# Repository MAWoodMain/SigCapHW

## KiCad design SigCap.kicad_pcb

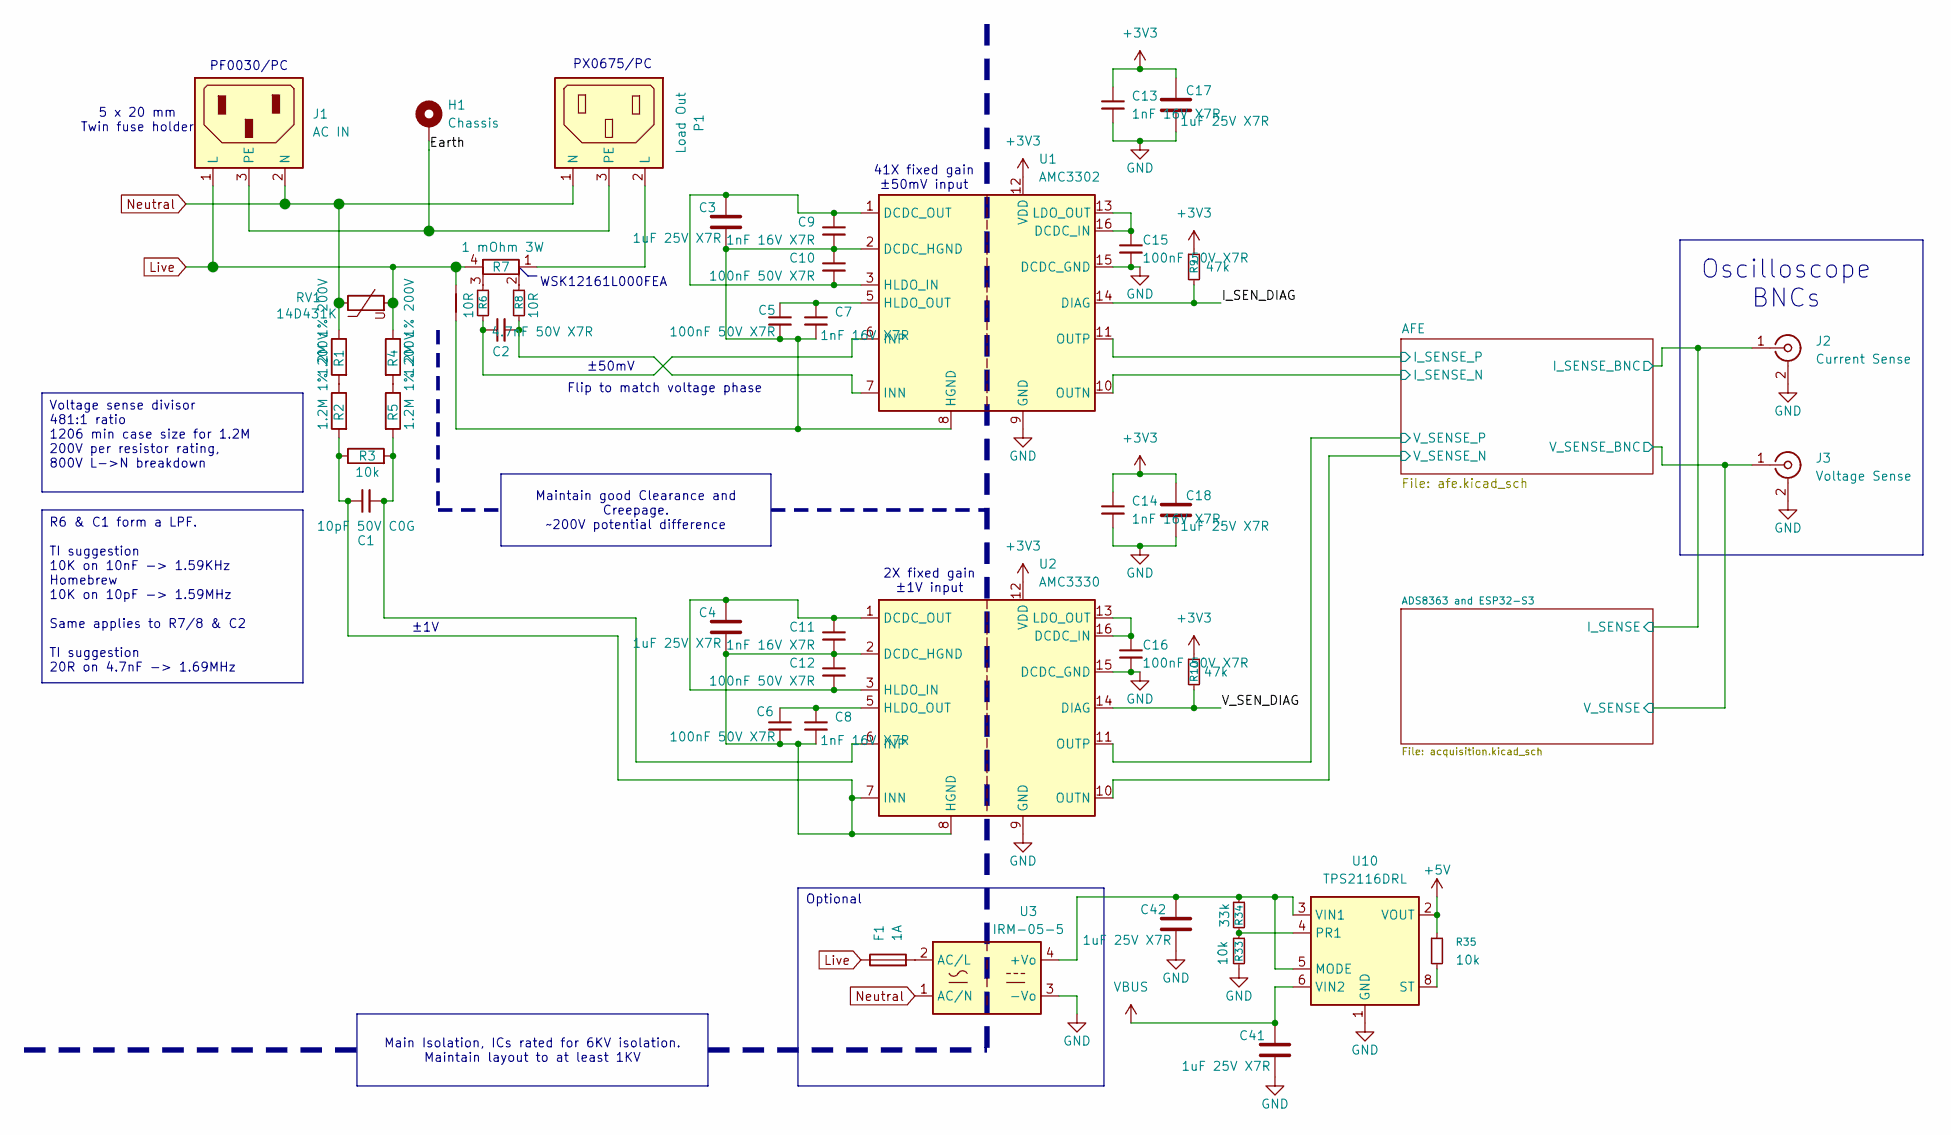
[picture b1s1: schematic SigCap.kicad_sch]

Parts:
C1: 10pF 50V C0G; C_0402_1005Metric; MPN GCM1555C1H100FA16D; LCSC Part # C161145
C2: 4.7nF 50V X7R; C_0402_1005Metric; MPN CL05B472KB5VPNC; LCSC Part # C307338
C3, C4, C17, C18, C41, C42: 1uF 25V X7R; C_0603_1608Metric; MPN GRM188R71E105KA12D; LCSC Part # C86020
C5, C6, C10, C12, C15, C16: 100nF 50V X7R; C_0402_1005Metric; MPN CC0402KRX7R9BB104; LCSC Part # C131394
C7, C8, C9, C11, C13, C14: 1nF 16V X7R; C_0402_1005Metric; MPN CC0402KRX7R7BB102; LCSC Part # C189467
F1: 1A; Fuse_Littelfuse_372_D8.50mm; MPN 38211000000; LCSC Part # C142712
H1: Chassis; 63849-1
J1: AC IN; PF0030PC; MPN PF0030/PC
J2: Current Sense; BNC_Amphenol_B6252HB-NPP3G-50_Horizontal; MPN B6252HB-NPP3G-50; LCSC Part # C22457552
J3: Voltage Sense; BNC_Amphenol_B6252HB-NPP3G-50_Horizontal; MPN B6252HB-NPP3G-50; LCSC Part # C22457552
NT1: L->HGND; NetTie-2_SMD_Pad0.5mm
P1: Load Out; PX0675PC; MPN PX0675/PC; LCSC Part # C3095293
R1, R2, R4, R5: 1.2M 1% 200V; R_1206_3216Metric; MPN CRCW12061M20FKEA; LCSC Part # C2085747
R3, R33, R35: 10k; R_0402_1005Metric; MPN 0402WGF1002TCE; LCSC Part # C25744
R6, R8: 10R; R_0402_1005Metric; MPN 0402WGF100JTCE; LCSC Part # C25077
R7: 1 mOhm 3W; WSK1216; MPN WSK12161L000FEA; LCSC Part # C844476
R9, R10: 47k; R_0402_1005Metric; MPN 0402WGF4702TCE; LCSC Part # C25792
R34: 33k; R_0402_1005Metric; MPN 0402WGF3302TCE; LCSC Part # C25779
RV1: 14D431K; RV_Disc_D15.5mm_W5.2mm_P7.5mm; MPN MOV-14D431K; LCSC Part # C1527438
U1: AMC3302; SOIC-16W_7.5x10.3mm_P1.27mm; MPN AMC3302DWER; LCSC Part # C4990160
U2: AMC3330; SOIC-16W_7.5x10.3mm_P1.27mm; MPN AMC3330DWER; LCSC Part # C2999368
U3: IRM-05-5; Converter_ACDC_MeanWell_IRM-05-xx_THT; MPN IRM-05-5; LCSC Part # C48603696
U10: TPS2116DRL; SOT-583-8; MPN TPS2116DRLR; LCSC Part # C3235557

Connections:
+3V3: C13.1, C14.1, C17.1, C18.1, R9.1, R10.1, U1.12 (VDD), U2.12 (VDD); also elsewhere on the board
+5V: C42.1, R34.1, U3.4 (+Vo), U10.3 (VIN1), U10.5 (MODE); also elsewhere on the board
/ADS8363 and ESP32-S3/I_SENSE: J2.1 (In); also elsewhere on the board
/ADS8363 and ESP32-S3/V_SENSE: J3.1 (In); also elsewhere on the board
/AFE/I_SENSE_N: U1.10 (OUTN); also elsewhere on the board
/AFE/I_SENSE_P: U1.11 (OUTP); also elsewhere on the board
/AFE/V_SENSE_N: U2.10 (OUTN); also elsewhere on the board
/AFE/V_SENSE_P: U2.11 (OUTP); also elsewhere on the board
/Earth: H1.1 (1_1), J1.3 (PE), P1.3 (PE)
/I_SEN_DIAG: R9.2, U1.14 (DIAG)
/V_SEN_DIAG: R10.2, U2.14 (DIAG)
GND: C13.2, C14.2, C15.2, C16.2, C17.2, C18.2, C41.2, C42.2, J2.2 (Ext), J3.2 (Ext), R33.2, U1.9 (GND), U1.15 (DCDC_GND), U2.9 (GND), U2.15 (DCDC_GND), U3.3 (-Vo), U10.1 (GND); also elsewhere on the board
Live: F1.1, J1.1 (L), NT1.2, R4.1, R7.4, RV1.2
unnamed: C41.1, U10.6 (VIN2)
unnamed: P1.2 (L), R7.1
unnamed: R1.2, R2.1
unnamed: R4.2, R5.1
unnamed: R6.1, R7.3
unnamed: R7.2, R8.1
unnamed: R33.1, R34.2, U10.4 (PR1)
unnamed: R35.1, U10.2 (VOUT), U10.7 (VOUT)
unnamed: R35.2, U10.8 (ST)
unnamed: C3.2, C5.2, C7.2, C9.2, C10.1, NT1.1, U1.2 (DCDC_HGND), U1.8 (HGND)
unnamed: C15.1, U1.13 (LDO_OUT), U1.16 (DCDC_IN)
unnamed: C3.1, C9.1, C10.2, U1.1 (DCDC_OUT), U1.3 (HLDO_IN)
unnamed: C5.1, C7.1, U1.5 (HLDO_OUT)
unnamed: C2.1, R8.2, U1.7 (INN)
unnamed: C2.2, R6.2, U1.6 (INP)
unnamed: C1.1, C4.2, C6.2, C8.2, C11.2, C12.1, R2.2, R3.1, U2.2 (DCDC_HGND), U2.7 (INN), U2.8 (HGND)
unnamed: C16.1, U2.13 (LDO_OUT), U2.16 (DCDC_IN)
unnamed: C4.1, C11.1, C12.2, U2.1 (DCDC_OUT), U2.3 (HLDO_IN)
unnamed: C6.1, C8.1, U2.5 (HLDO_OUT)
unnamed: C1.2, R3.2, R5.2, U2.6 (INP)
unnamed: F1.2, U3.2 (AC/L)
Neutral: J1.2 (N), P1.1 (N), R1.1, RV1.1, U3.1 (AC/N)

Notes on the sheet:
PF0030/PC
PX0675/PC
±50mV
41X fixed gain ±50mV input
Oscilloscope BNCs
Optional
WSK12161L000FEA
±1V
Flip to match voltage phase
5 x 20 mm Twin fuse holder
2X fixed gain ±1V input
Voltage sense divisor 481:1 ratio 1206 min case size for 1.2M 200V per resistor rating, 800V L->N breakdown
Maintain good Clearance and Creepage. ~200V potential difference
Main Isolation, ICs rated for 6KV isolation. Maintain layout to at least 1KV
R6 & C1 form a LPF. TI suggestion 10K on 10nF -> 1.59KHz Homebrew 10K on 10pF -> 1.59MHz Same applies to R7/8 & C2 TI suggestion 20R on 4.7nF -> 1.69MHz

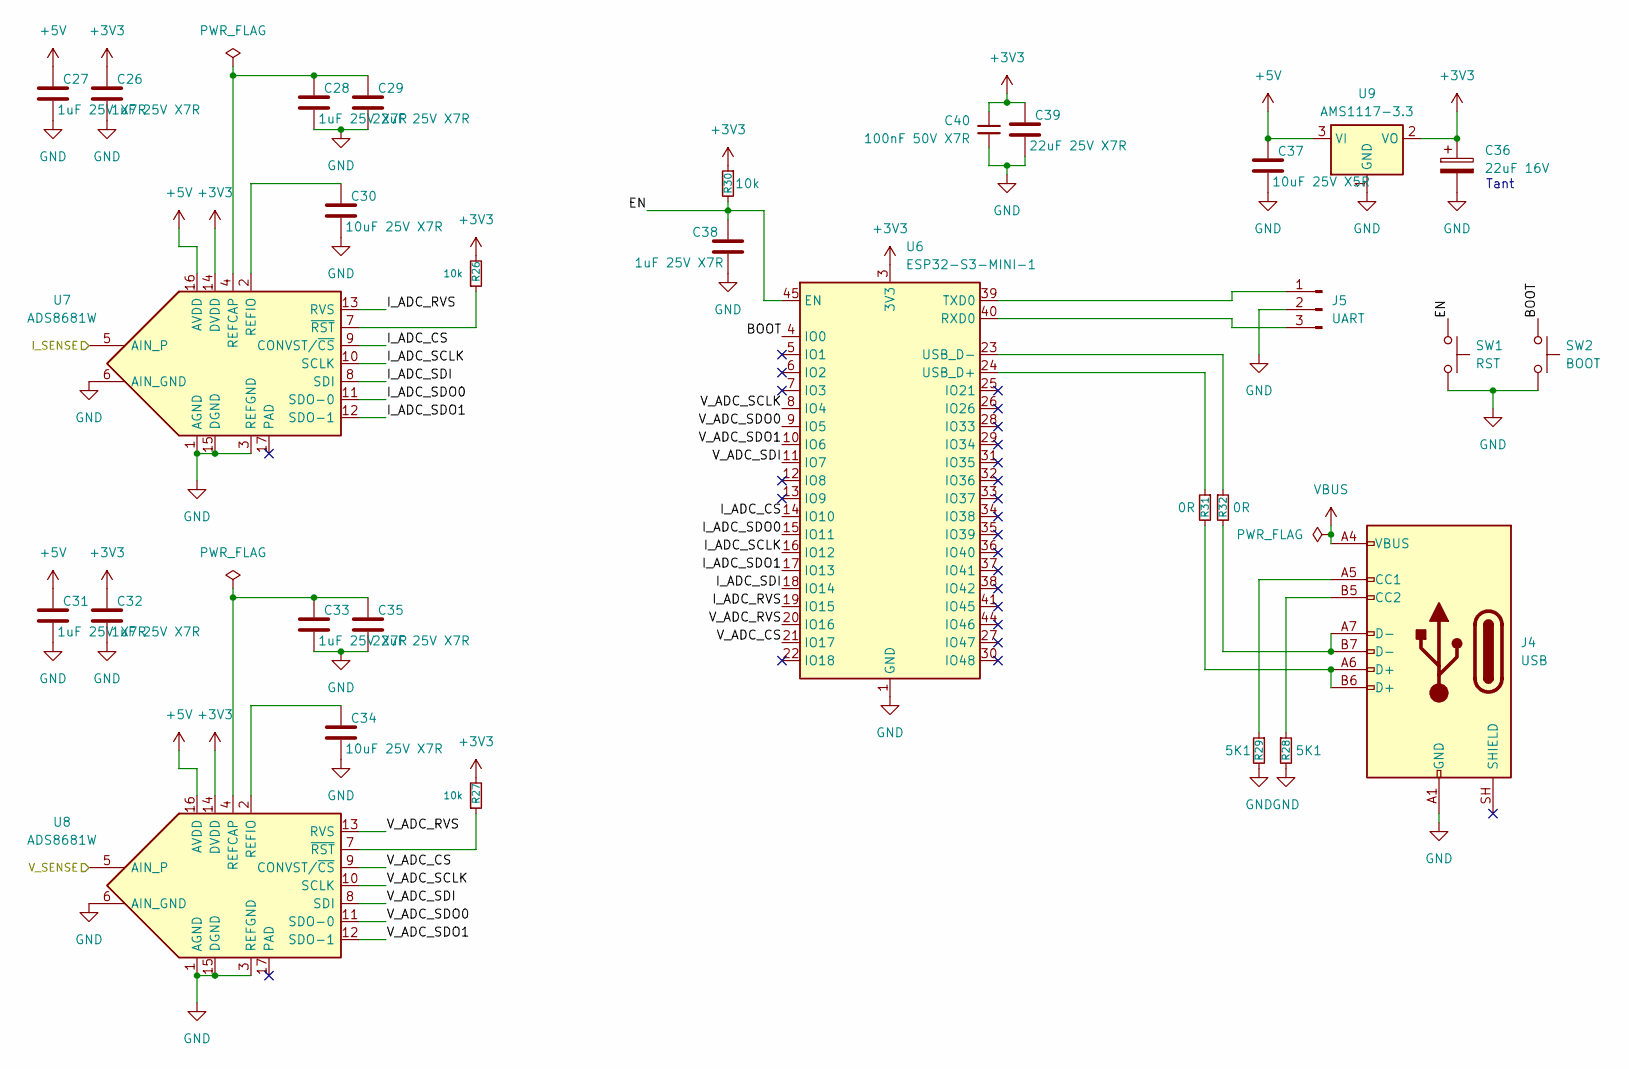
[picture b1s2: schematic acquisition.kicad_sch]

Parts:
C26, C27, C28, C31, C32, C33, C38: 1uF 25V X7R; C_0603_1608Metric; MPN GRM188R71E105KA12D; LCSC Part # C86020
C29, C35, C39: 22uF 25V X7R; C_1210_3225Metric; MPN GRM32ER71E226KE15L; LCSC Part # C21397
C30, C34: 10uF 25V X7R; C_1206_3216Metric; MPN GRM31CR71E106KA12L; LCSC Part # C77093
C36: 22uF 16V; CP_EIA-3528-21_Kemet-B; MPN TPSB226K016R0600; LCSC Part # C1952809
C37: 10uF 25V X5R; C_1206_3216Metric; MPN CL31A106KAHNNNE; LCSC Part # C9807
C40: 100nF 50V X7R; C_0402_1005Metric; MPN CC0402KRX7R9BB104; LCSC Part # C131394
J4: USB; USB_C_Receptacle_GCT_USB4105-xx-A_16P_TopMnt_Horizontal; MPN USB4105-GF-A; LCSC Part # C3020560
J5: UART; PinHeader_1x03_P2.54mm_Vertical; MPN TSW-103-07-G-S; LCSC Part # C3335811
R26, R27, R30: 10k; R_0402_1005Metric; MPN 0402WGF1002TCE; LCSC Part # C25744
R28, R29: 5K1; R_0402_1005Metric; MPN 0402WGF5101TCE; LCSC Part # C25905
R31, R32: 0R; R_0402_1005Metric; MPN AC0402JR-070RL; LCSC Part # C138289
SW1: RST; SW_Tactile_SKHH_Angled; MPN SKHHLQA010; LCSC Part # C125034
SW2: BOOT; SW_Tactile_SKHH_Angled; MPN SKHHLQA010; LCSC Part # C125034
U6: ESP32-S3-MINI-1; ESP32-S2-MINI-1; MPN ESP32-S3-MINI-1-N4R2; LCSC Part # C3013941
U7, U8: ADS8681W; QFN-16-1EP_4x4mm_P0.65mm_EP2.7x2.7mm; MPN ADS8681WRUMT; LCSC Part # C41410098
U9: AMS1117-3.3; SOT-223-3_TabPin2; MPN AMS1117-3.3; LCSC Part # C6186

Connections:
+3V3: C26.1, C32.1, C36.1, C39.1, C40.1, R26.2, R27.2, R30.1, U6.3 (3V3), U7.14 (DVDD), U8.14 (DVDD), U9.2 (VO); also elsewhere on the board
+5V: C27.1, C31.1, C37.1, U7.16 (AVDD), U8.16 (AVDD), U9.3 (VI); also elsewhere on the board
/ADS8363 and ESP32-S3/BOOT: SW2.1, U6.4 (IO0)
/ADS8363 and ESP32-S3/EN: C38.1, R30.2, SW1.1, U6.45 (EN)
/ADS8363 and ESP32-S3/I_ADC_CS: U6.14 (IO10), U7.9 (CONVST/~CS)
/ADS8363 and ESP32-S3/I_ADC_RVS: U6.19 (IO15), U7.13 (RVS)
/ADS8363 and ESP32-S3/I_ADC_SCLK: U6.16 (IO12), U7.10 (SCLK)
/ADS8363 and ESP32-S3/I_ADC_SDI: U6.18 (IO14), U7.8 (SDI)
/ADS8363 and ESP32-S3/I_ADC_SDO0: U6.15 (IO11), U7.11 (SDO-0)
/ADS8363 and ESP32-S3/I_ADC_SDO1: U6.17 (IO13), U7.12 (SDO-1)
/ADS8363 and ESP32-S3/I_SENSE: U7.5 (AIN_P); also elsewhere on the board
/ADS8363 and ESP32-S3/V_ADC_CS: U6.21 (IO17), U8.9 (CONVST/~CS)
/ADS8363 and ESP32-S3/V_ADC_RVS: U6.20 (IO16), U8.13 (RVS)
/ADS8363 and ESP32-S3/V_ADC_SCLK: U6.8 (IO4), U8.10 (SCLK)
/ADS8363 and ESP32-S3/V_ADC_SDI: U6.11 (IO7), U8.8 (SDI)
/ADS8363 and ESP32-S3/V_ADC_SDO0: U6.9 (IO5), U8.11 (SDO-0)
/ADS8363 and ESP32-S3/V_ADC_SDO1: U6.10 (IO6), U8.12 (SDO-1)
/ADS8363 and ESP32-S3/V_SENSE: U8.5 (AIN_P); also elsewhere on the board
GND: C26.2, C27.2, C28.2, C29.2, C30.2, C31.2, C32.2, C33.2, C34.2, C35.2, C36.2, C37.2, C38.2, C39.2, C40.2, J4.A1 (GND), J4.A12 (GND), J4.B1 (GND), J4.B12 (GND), J5.2, R28.2, R29.2, SW1.2, SW2.2, U6.1 (GND), U6.2 (GND), U6.42 (GND), U6.43 (GND), U6.46 (GND), U6.47 (GND), U6.48 (GND), U6.49 (GND), U6.50 (GND), U6.51 (GND), U6.52 (GND), U6.53 (GND), U6.54 (GND), U6.55 (GND), U6.56 (GND), U6.57 (GND), U6.58 (GND), U6.59 (GND), U6.60 (GND), U6.61 (GND), U6.62 (GND), U6.63 (GND), U6.64 (GND), U6.65 (GND), U7.1 (AGND), U7.3 (REFGND), U7.6 (AIN_GND), U7.15 (DGND), U8.1 (AGND), U8.3 (REFGND), U8.6 (AIN_GND), U8.15 (DGND), U9.1 (GND); also elsewhere on the board
unnamed: J4.A5 (CC1), R29.1
unnamed: J4.B5 (CC2), R28.1
unnamed: J4.A6 (D+), J4.B6 (D+), R31.2
unnamed: J4.A7 (D-), J4.B7 (D-), R32.2
unnamed: J5.1, U6.39 (TXD0)
unnamed: J5.3, U6.40 (RXD0)
unnamed 38: J4.A4 (VBUS), J4.A9 (VBUS), J4.B4 (VBUS), J4.B9 (VBUS); also elsewhere on the board
unnamed: R31.1, U6.24 (USB_D+)
unnamed: R32.1, U6.23 (USB_D-)
unnamed: C28.1, C29.1, U7.4 (REFCAP)
unnamed: C30.1, U7.2 (REFIO)
unnamed: R26.1, U7.7 (~RST)
unnamed: C33.1, C35.1, U8.4 (REFCAP)
unnamed: C34.1, U8.2 (REFIO)
unnamed: R27.1, U8.7 (~RST)

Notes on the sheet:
Tant

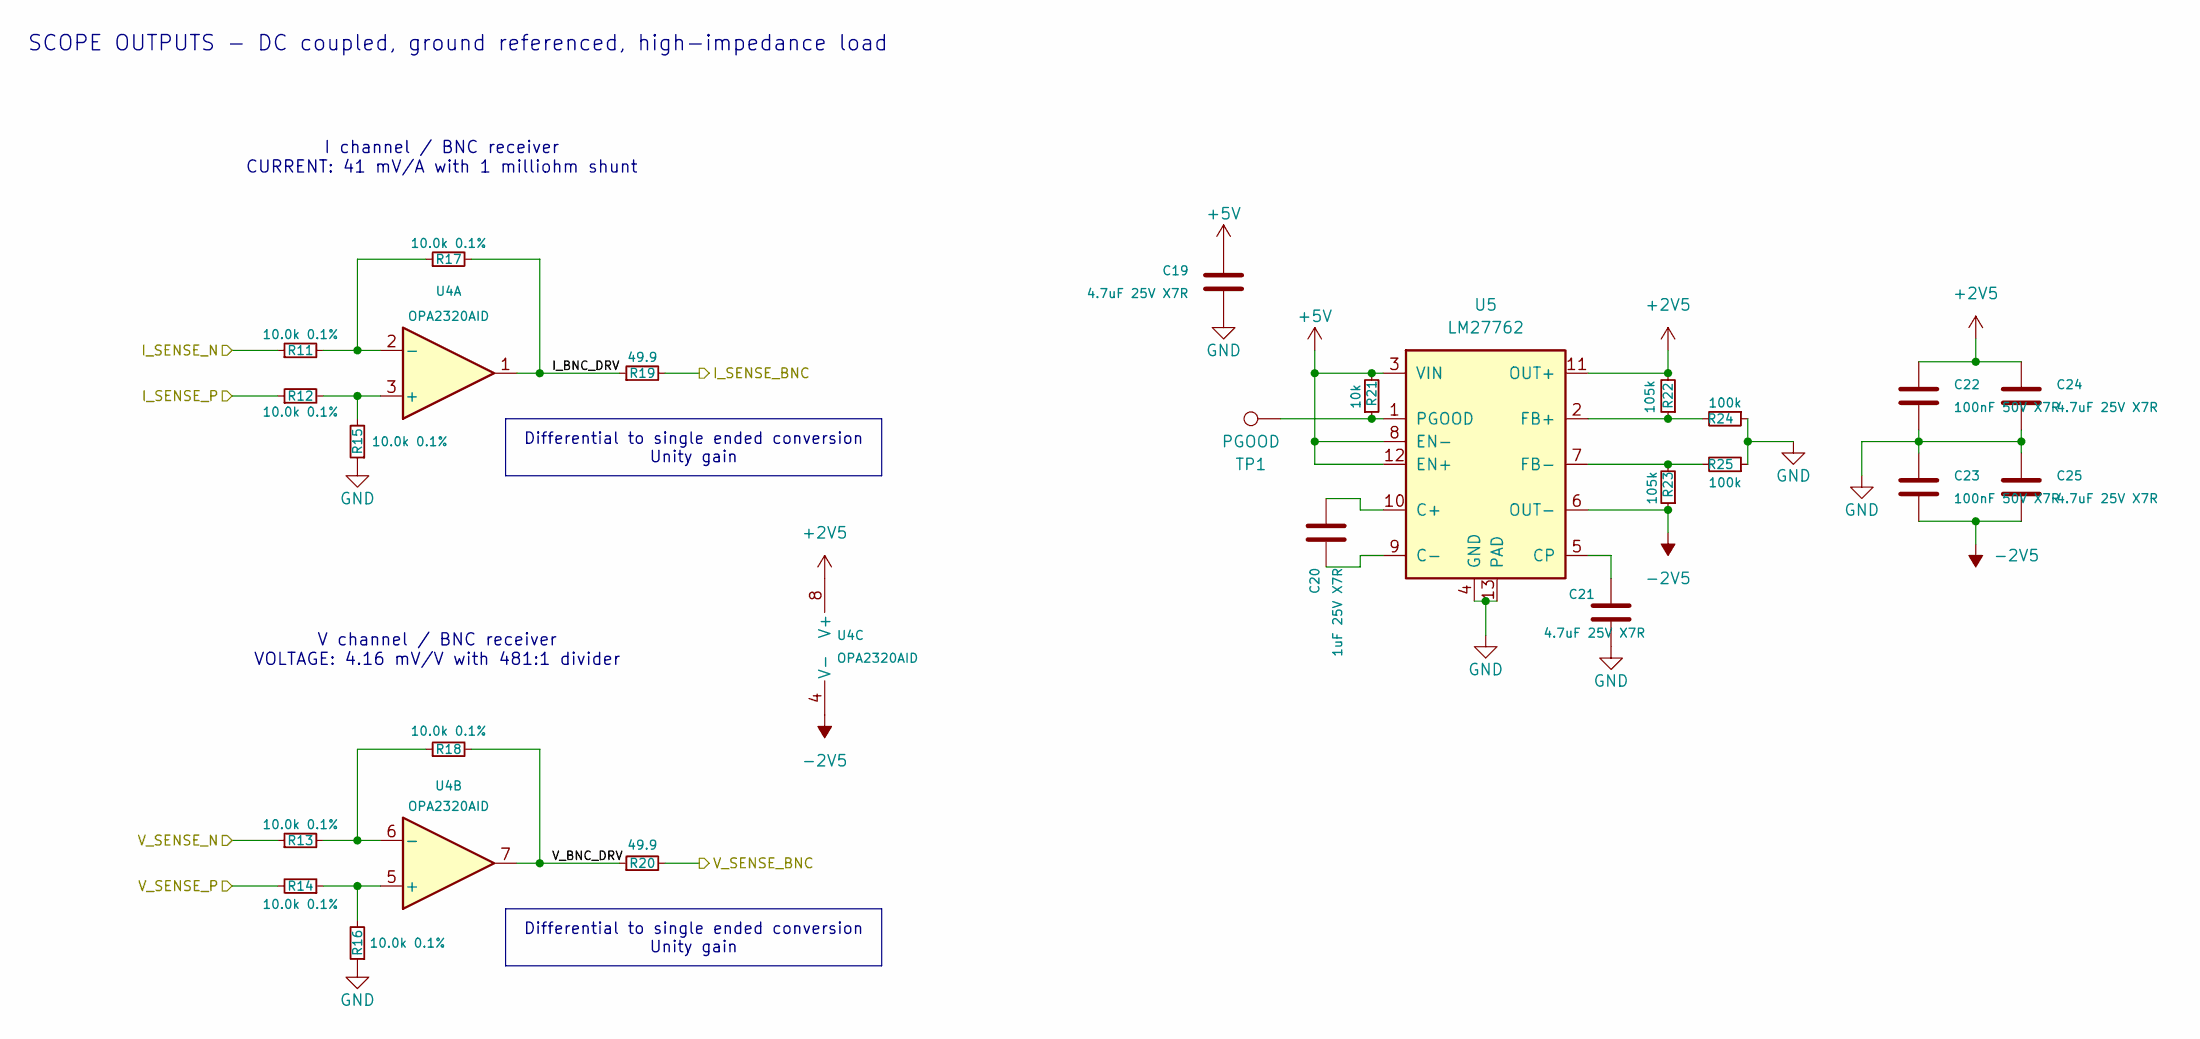
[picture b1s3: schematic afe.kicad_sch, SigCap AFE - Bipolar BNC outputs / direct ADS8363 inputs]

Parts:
C19, C21, C24, C25: 4.7uF 25V X7R; C_1206_3216Metric; MPN CL31B475KAHNNNE; LCSC Part # C1872
C20: 1uF 25V X7R; C_0603_1608Metric; MPN GRM188R71E105KA12D; LCSC Part # C86020
C22, C23: 100nF 50V X7R; C_0402_1005Metric; MPN CC0402KRX7R9BB104; LCSC Part # C131394
R11, R12, R13, R14, R15, R16, R17, R18: 10.0k 0.1%; R_0402_1005Metric; MPN RT0402BRD0710KL; LCSC Part # C190095
R19, R20: 49.9; R_0402_1005Metric; MPN 0402WGF499JTCE; LCSC Part # C25120
R21: 10k; R_0402_1005Metric; MPN 0402WGF1002TCE; LCSC Part # C25744
R22, R23: 105k; R_0402_1005Metric; MPN 0402WGF1053TCE; LCSC Part # C25742
R24, R25: 100k; R_0402_1005Metric; MPN 0402WGF1003TCE; LCSC Part # C25741
TP1: PGOOD; TestPoint_Keystone_5000-5004_Miniature; MPN 5000; LCSC Part # C5199900
U4: OPA2320AID; SOIC-8_3.9x4.9mm_P1.27mm; MPN OPA2320AIDR; LCSC Part # C2863402
U5: LM27762; WSON-12-1EP_3x2mm_P0.5mm_EP1x2.65_ThermalVias; MPN LM27762DSSR; LCSC Part # C473398

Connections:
+2V5: C22.2, C24.2, R22.2, U4.8 (V+), U5.11 (OUT+)
+5V: C19.2, R21.2, U5.3 (VIN), U5.8 (EN-), U5.12 (EN+); also elsewhere on the board
-2V5: C23.2, C25.1, R23.1, U4.4 (V-), U5.6 (OUT-)
/ADS8363 and ESP32-S3/I_SENSE: R19.2; also elsewhere on the board
/ADS8363 and ESP32-S3/V_SENSE: R20.2; also elsewhere on the board
/AFE/I_BNC_DRV: R17.2, R19.1, U4.1
/AFE/I_SENSE_N: R11.1; also elsewhere on the board
/AFE/I_SENSE_P: R12.1; also elsewhere on the board
/AFE/V_BNC_DRV: R18.2, R20.1, U4.7
/AFE/V_SENSE_N: R13.1; also elsewhere on the board
/AFE/V_SENSE_P: R14.2; also elsewhere on the board
GND: C19.1, C21.1, C22.1, C23.1, C24.1, C25.2, R15.1, R16.1, R24.1, R25.1, U5.4 (GND), U5.13 (PAD); also elsewhere on the board
unnamed: R12.2, R15.2, U4.3 (+)
unnamed: R11.2, R17.1, U4.2 (-)
unnamed: R14.1, R16.2, U4.5 (+)
unnamed: R13.2, R18.1, U4.6 (-)
unnamed: C20.1, U5.10 (C+)
unnamed: C20.2, U5.9 (C-)
unnamed: C21.2, U5.5 (CP)
unnamed: R22.1, R24.2, U5.2 (FB+)
unnamed: R23.2, R25.2, U5.7 (FB-)
unnamed: R21.1, TP1.1 (1_1), U5.1 (PGOOD)

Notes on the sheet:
I channel / BNC receiver CURRENT: 41 mV/A with 1 milliohm shunt
V channel / BNC receiver VOLTAGE: 4.16 mV/V with 481:1 divider
SCOPE OUTPUTS - DC coupled, ground referenced, high-impedance load
Differential to single ended conversion Unity gain

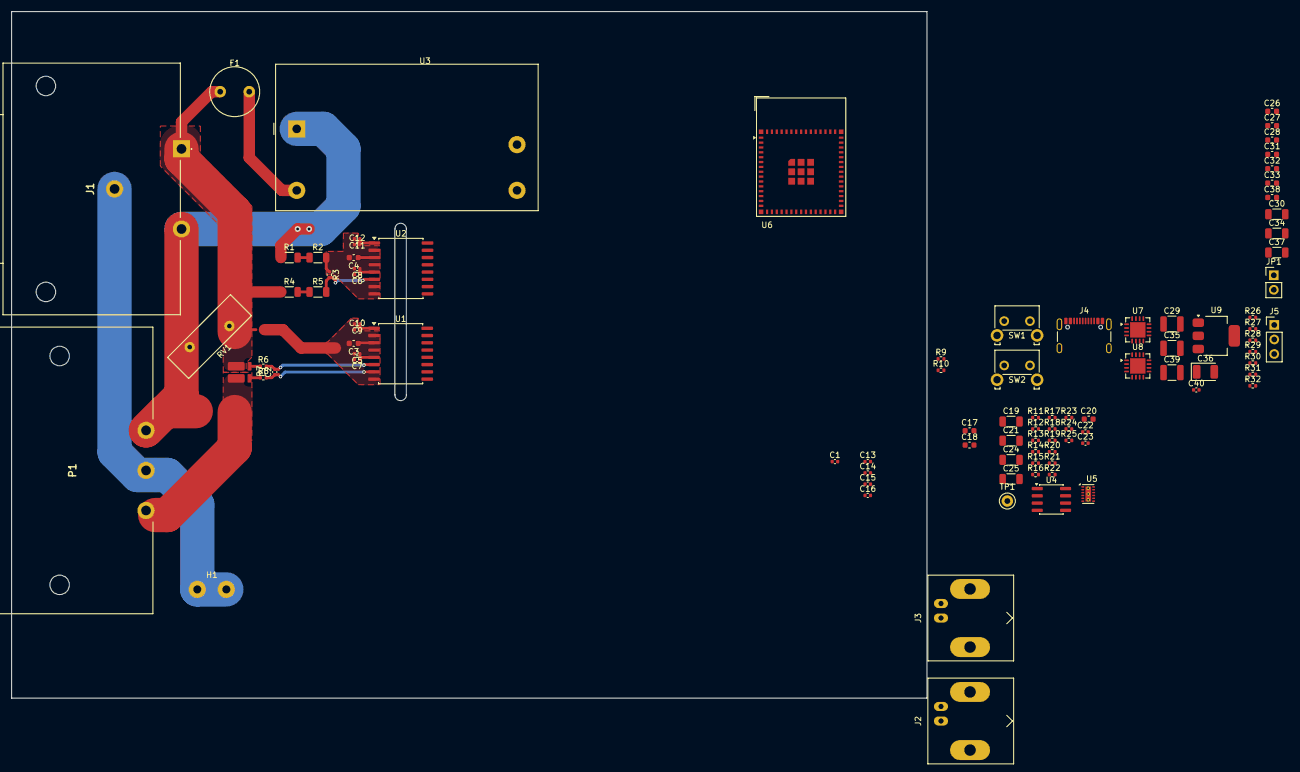
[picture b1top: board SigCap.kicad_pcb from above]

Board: 2 copper layers, 160.0 x 120.0 mm, 95 parts (0 on the bottom side), 74 nets.

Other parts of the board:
JP1: USB Power; PinHeader_1x02_P2.54mm_Vertical

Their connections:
+5V: JP1.2 (B); also elsewhere on the board
unnamed 38: JP1.1 (A); also elsewhere on the board

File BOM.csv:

Comment,Designator,Footprint,LCSC Part #,MPN,Quantity,JLC stock on 2026-11-07,Unit USD,JLC listing,Notes
10pF 50V C0G,C1,Capacitor_SMD:C_0402_1005Metric,C161145,GCM1555C1H100FA16D,1,40048,0.0185,https://jlcpcb.com/partdetail/C161145,
4.7nF 50V X7R,C2,Capacitor_SMD:C_0402_1005Metric,C307338,CL05B472KB5VPNC,1,5665,0.0174,https://jlcpcb.com/partdetail/C307338,
1nF 16V X7R,"C7,C8,C9,C11,C13,C14",Capacitor_SMD:C_0402_1005Metric,C189467,CC0402KRX7R7BB102,6,561800,0.0022,https://jlcpcb.com/partdetail/C189467,
100nF 50V X7R,"C5,C6,C10,C12,C15,C16,C22,C23,C40",Capacitor_SMD:C_0402_1005Metric,C131394,CC0402KRX7R9BB104,9,10928519,0.0106,https://jlcpcb.com/partdetail/C131394,
1uF 25V X7R,"C3,C4,C17,C18,C20,C26,C27,C28,C31,C32,C33,C38,C41,C42",Capacitor_SMD:C_0603_1608Metric,C86020,GRM188R71E105KA12D,14,79353,0.0473,https://jlcpcb.com/partdetail/C86020,
4.7uF 25V X7R,"C19,C21,C24,C25",Capacitor_SMD:C_1206_3216Metric,C1872,CL31B475KAHNNNE,4,66925,0.0622,https://jlcpcb.com/partdetail/C1872,
10uF 25V X7R,"C30,C34",Capacitor_SMD:C_1206_3216Metric,C77093,GRM31CR71E106KA12L,2,138577,0.2372,https://jlcpcb.com/partdetail/C77093,
10uF 25V X5R,C37,Capacitor_SMD:C_1206_3216Metric,C9807,CL31A106KAHNNNE,1,666005,0.0537,https://jlcpcb.com/partdetail/C9807,
22uF 25V X7R,"C29,C35,C39",Capacitor_SMD:C_1210_3225Metric,C21397,GRM32ER71E226KE15L,3,72247,0.404,https://jlcpcb.com/partdetail/C21397,
22uF 16V,C36,Capacitor_Tantalum_SMD:CP_EIA-3528-21_Kemet-B,C1952809,TPSB226K016R0600,1,431,1.0631,https://jlcpcb.com/partdetail/C1952809,
1.2M 1% 200V,"R1,R2,R4,R5",Resistor_SMD:R_1206_3216Metric,C2085747,CRCW12061M20FKEA,4,555,0.0552,https://jlcpcb.com/partdetail/C2085747,
10k,"R3,R21,R26,R27,R30,R33,R35",Resistor_SMD:R_0402_1005Metric,C25744,0402WGF1002TCE,7,22767958,0.0028,https://jlcpcb.com/partdetail/C25744,
33k,R34,Resistor_SMD:R_0402_1005Metric,C25779,0402WGF3302TCE,1,2226792,0.0019,https://jlcpcb.com/partdetail/C25779,
10R,"R6,R8",Resistor_SMD:R_0402_1005Metric,C25077,0402WGF100JTCE,2,2730843,0.0012,https://jlcpcb.com/partdetail/C25077,
47k,"R9,R10",Resistor_SMD:R_0402_1005Metric,C25792,0402WGF4702TCE,2,6133333,0.0019,https://jlcpcb.com/partdetail/C25792,
10.0k 0.1%,"R11,R12,R13,R14,R15,R16,R17,R18",Resistor_SMD:R_0402_1005Metric,C190095,RT0402BRD0710KL,8,1559595,0.0246,https://jlcpcb.com/partdetail/C190095,
49.9,"R19,R20",Resistor_SMD:R_0402_1005Metric,C25120,0402WGF499JTCE,2,1329025,0.0013,https://jlcpcb.com/partdetail/C25120,
105k,"R22,R23",Resistor_SMD:R_0402_1005Metric,C25742,0402WGF1053TCE,2,44658,0.0021,https://jlcpcb.com/partdetail/C25742,
100k,"R24,R25",Resistor_SMD:R_0402_1005Metric,C25741,0402WGF1003TCE,2,8298798,0.0013,https://jlcpcb.com/partdetail/C25741,
5K1,"R28,R29",Resistor_SMD:R_0402_1005Metric,C25905,0402WGF5101TCE,2,4548081,0.0023,https://jlcpcb.com/partdetail/C25905,
0R,"R31,R32",Resistor_SMD:R_0402_1005Metric,C138289,AC0402JR-070RL,2,2724027,0.0026,https://jlcpcb.com/partdetail/C138289,
1 mOhm 3W,R7,SigCap:WSK1216,C844476,WSK12161L000FEA,1,3754,0.8914,https://jlcpcb.com/partdetail/C844476,
14D431K,RV1,Varistor:RV_Disc_D15.5mm_W5.2mm_P7.5mm,C1527438,MOV-14D431K,1,220,0.4465,https://jlcpcb.com/partdetail/C1527438,
1A,F1,Fuse:Fuse_Littelfuse_372_D8.50mm,C142712,38211000000,1,2711,0.202,https://jlcpcb.com/partdetail/C142712,Littelfuse 382 TR5 body and lead geometry match the standard 372 land pattern.
Chassis,H1,SigCap:63849-1,C86469,63849-1,1,,,https://jlcpcb.com/partdetail/TeConnectivity-638491/C86469,PCB chassis bonding tab. Mating crimp is harness hardware.
AC IN,J1,SigCap:PF0030PC,,PF0030/PC,1,,,,Distributor supplied: Farnell UK 428784 (https://uk.farnell.com/bulgin/pf0030-pc/inlet-iec-fused-pcb-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 / DigiKey UK 708-1914-ND (https://www.digikey.co.uk/en/products/detail/bulgin/PF0030-P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 / RS 70427399 (US listing).
Load Out,P1,SigCap:PX0675PC,C3095293,PX0675/PC,1,33,4.6971,https://jlcpcb.com/partdetail/C3095293,
Current Sense,J2,Connector_Coaxial:BNC_Amphenol_B6252HB-NPP3G-50_Horizontal,C22457552,B6252HB-NPP3G-50,1,435,3.6324,https://jlcpcb.com/partdetail/C22457552,
Voltage Sense,J3,Connector_Coaxial:BNC_Amphenol_B6252HB-NPP3G-50_Horizontal,C22457552,B6252HB-NPP3G-50,1,435,3.6324,https://jlcpcb.com/partdetail/C22457552,
USB,J4,Connector_USB:USB_C_Receptacle_GCT_USB4105-xx-A_16P_TopMnt_Horizontal,C3020560,USB4105-GF-A,1,19231,1.0206,https://jlcpcb.com/partdetail/C3020560,Unused A8/B8 SBU pads remain unconnected.
UART,J5,Connector_PinHeader_2.54mm:PinHeader_1x03_P2.54mm_Vertical,C3335811,TSW-103-07-G-S,1,1688,0.3456,https://jlcpcb.com/partdetail/C3335811,
RST,SW1,Button_Switch_THT:SW_Tactile_SKHH_Angled,C125034,SKHHLQA010,1,2250,0.1502,https://jlcpcb.com/partdetail/C125034,8.35 mm stem. KiCad outline shows the 5.85 mm variant.
BOOT,SW2,Button_Switch_THT:SW_Tactile_SKHH_Angled,C125034,SKHHLQA010,1,2250,0.1502,https://jlcpcb.com/partdetail/C125034,8.35 mm stem. KiCad outline shows the 5.85 mm variant.
PGOOD,TP1,TestPoint:TestPoint_Keystone_5000-5004_Miniature,C5199900,5000,1,4174,0.3031,https://jlcpcb.com/partdetail/C5199900,
AMC3302,U1,Package_SO:SOIC-16W_7.5x10.3mm_P1.27mm,C4990160,AMC3302DWER,1,246,3.2203,https://jlcpcb.com/partdetail/C4990160,
AMC3330,U2,Package_SO:SOIC-16W_7.5x10.3mm_P1.27mm,C2999368,AMC3330DWER,1,2086,4.9866,https://jlcpcb.com/partdetail/C2999368,
IRM-05-5,U3,Converter_ACDC:Converter_ACDC_MeanWell_IRM-05-xx_THT,C48603696,IRM-05-5,1,3237,4.926,https://jlcpcb.com/partdetail/C48603696,Optional onboard mains supply.
OPA2320AID,U4,Package_SO:SOIC-8_3.9x4.9mm_P1.27mm,C2863402,OPA2320AIDR,1,5569,2.6053,https://jlcpcb.com/partdetail/C2863402,
LM27762,U5,Package_SON:WSON-12-1EP_3x2mm_P0.5mm_EP1x2.65_ThermalVias,C473398,LM27762DSSR,1,40338,0.9617,https://jlcpcb.com/partdetail/C473398,
ESP32-S3-MINI-1,U6,RF_Module:ESP32-S2-MINI-1,C3013941,ESP32-S3-MINI-1-N4R2,1,7494,5.0046,https://jlcpcb.com/partdetail/C3013941,N4R2 variant provides 2 MB PSRAM for capture buffering.
ADS8681W,"U7,U8",Package_DFN_QFN:QFN-16-1EP_4x4mm_P0.65mm_EP2.7x2.7mm,C41410098,ADS8681WRUMT,2,31,12.333,https://jlcpcb.com/partdetail/C41410098,
AMS1117-3.3,U9,Package_TO_SOT_SMD:SOT-223-3_TabPin2,C6186,AMS1117-3.3,1,1612224,0.206,https://jlcpcb.com/partdetail/C6186,
TPS2116DRL,U10,Package_TO_SOT_SMD:SOT-583-8,C3235557,TPS2116DRLR,1,53290,0.3877,https://jlcpcb.com/partdetail/C3235557,
